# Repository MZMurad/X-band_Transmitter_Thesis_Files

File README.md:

# X-band_Transmitter_Thesis_Files
This is a repo for all the files used and mentioned in my thesis

The file structure:
    
- Hardware: Includes all KiCad schematics and PCBs, all are KiCad projects
- All GNU Radio flow graphs wthin the GNU labeled folder
- The python folder contains all python used for plotting and test automation for the HP5262A VNA and the HP8562A Spectrum Analyzer
- The data folder contains all data collected over the span of this thesis

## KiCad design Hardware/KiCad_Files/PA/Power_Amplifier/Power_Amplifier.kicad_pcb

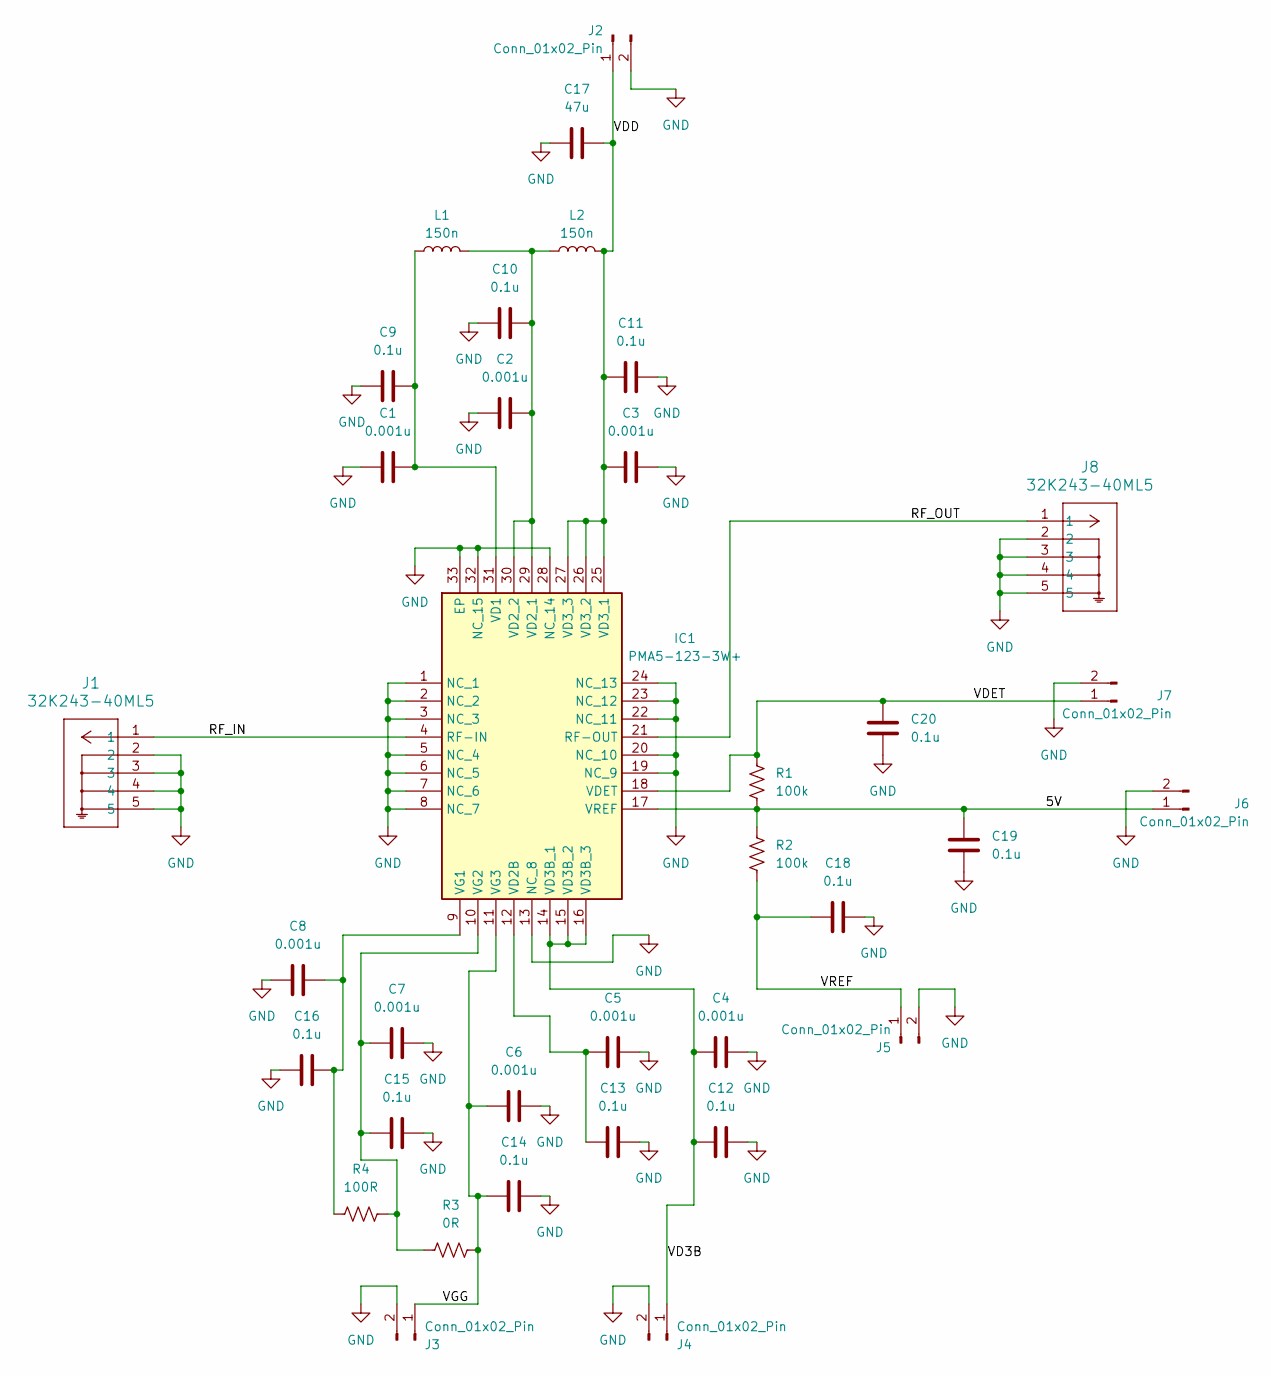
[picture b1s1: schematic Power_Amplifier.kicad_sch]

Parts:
C1, C2, C3, C4, C5, C6, C7, C8: 0.001u; C_0402_1005Metric_Pad0.74x0.62mm_HandSolder
C9, C10, C11, C12, C13, C14, C15, C16, C18, C19, C20: 0.1u; C_0402_1005Metric_Pad0.74x0.62mm_HandSolder
C17: 47u; C_1206_3216Metric
IC1: PMA5-123-3W+; QFN50P500X500X100-33N-D; Manufacturer_Part_Number PMA5-123-3W+
J1, J8: 32K243-40ML5; CONN_32K243-40ML5_RBG
J2, J3, J4, J5, J6, J7: Conn_01x02_Pin; PinHeader_1x02_P2.54mm_Vertical
L1, L2: 150n; L_0402_1005Metric_Pad0.77x0.64mm_HandSolder
R1, R2: 100k; R_0402_1005Metric_Pad0.72x0.64mm_HandSolder
R3: 0R; R_0402_1005Metric_Pad0.72x0.64mm_HandSolder
R4: 100R; R_0402_1005Metric_Pad0.72x0.64mm_HandSolder

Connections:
/5V: C19.1, IC1.17 (VREF), J6.1, R1.2, R2.1
/RF_IN: IC1.4 (RF-IN), J1.1
/RF_OUT: IC1.21 (RF-OUT), J8.1
/VD3B: C4.2, C12.2, IC1.14 (VD3B_1), IC1.15 (VD3B_2), IC1.16 (VD3B_3), J4.1
/VDD: C3.2, C11.1, C17.2, IC1.25 (VD3_1), IC1.26 (VD3_2), IC1.27 (VD3_3), J2.1, L2.2
/VDET: C20.1, IC1.18 (VDET), J7.1, R1.1
/VGG: C6.2, C14.2, IC1.11 (VG3), J3.1, R3.2
/VREF: C18.2, J5.1, R2.2
GND: C1.1, C2.1, C3.1, C4.1, C5.1, C6.1, C7.1, C8.1, C9.1, C10.1, C11.2, C12.1, C13.1, C14.1, C15.1, C16.1, C17.1, C18.1, C19.2, C20.2, IC1.1 (NC_1), IC1.2 (NC_2), IC1.3 (NC_3), IC1.5 (NC_4), IC1.6 (NC_5), IC1.7 (NC_6), IC1.8 (NC_7), IC1.13 (NC_8), IC1.19 (NC_9), IC1.20 (NC_10), IC1.22 (NC_11), IC1.23 (NC_12), IC1.24 (NC_13), IC1.28 (NC_14), IC1.32 (NC_15), IC1.33 (EP), J1.2, J1.3, J1.4, J1.5, J2.2, J3.2, J4.2, J5.2, J6.2, J7.2, J8.2, J8.3, J8.4, J8.5
unnamed: C1.2, C9.2, IC1.31 (VD1), L1.1
unnamed: C5.2, C13.2, IC1.12 (VD2B)
unnamed: C2.2, C10.2, IC1.29 (VD2_1), IC1.30 (VD2_2), L1.2, L2.1
unnamed: C8.2, C16.2, IC1.9 (VG1), R4.1
unnamed: C7.2, C15.2, IC1.10 (VG2), R3.1, R4.2

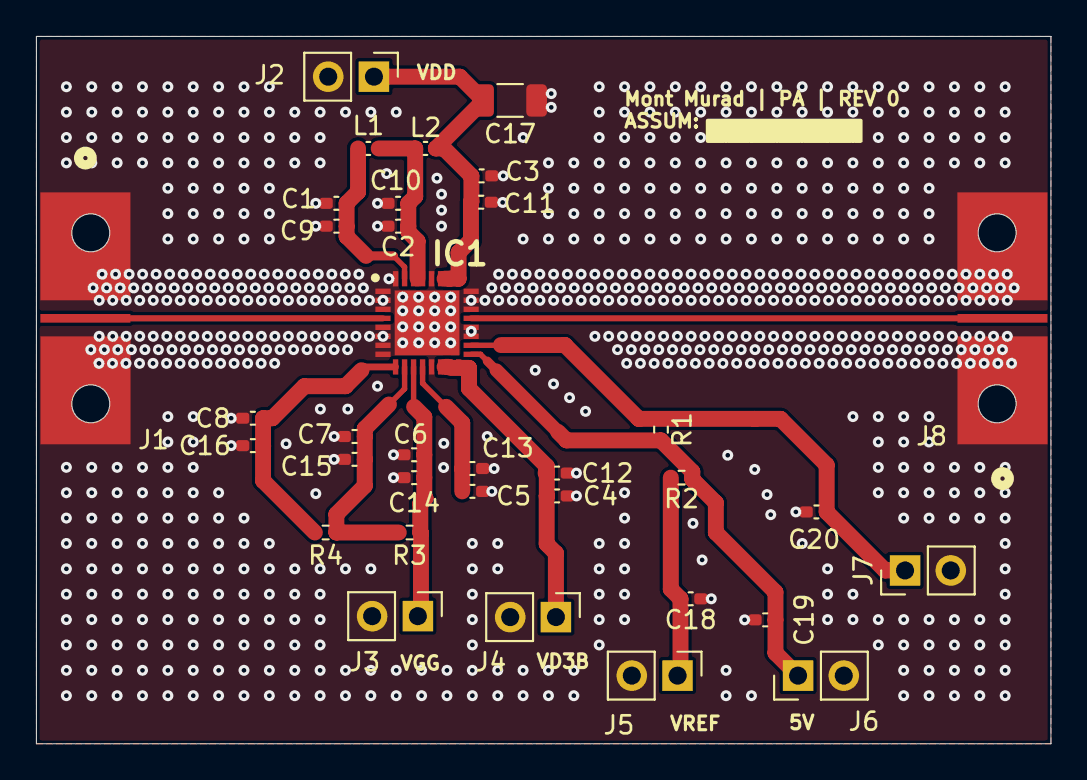
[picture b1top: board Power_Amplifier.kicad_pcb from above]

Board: 4 copper layers, 56.4 x 39.3 mm, 35 parts (0 on the bottom side), 14 nets.

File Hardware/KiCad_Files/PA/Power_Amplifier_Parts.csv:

"Reference","Value","Datasheet","Footprint","Qty","DNP"
"C1,C2,C3,C4,C5,C6,C7,C8","0.001u","~","Capacitor_SMD:C_0402_1005Metric_Pad0.74x0.62mm_HandSolder","8",""
"C9,C10,C11,C12,C13,C14,C15,C16,C18,C19,C20","0.1u","~","Capacitor_SMD:C_0402_1005Metric_Pad0.74x0.62mm_HandSolder","11",""
"C17","47u","~","Capacitor_SMD:C_1206_3216Metric","1",""
"IC1","PMA5-123-3W+","https://www.minicircuits.com/pdfs/PMA5-123-3W+.pdf","PMA5-123-3W+:QFN50P500X500X100-33N-D","1",""
"J1,J8","32K243-40ML5","32K243-40ML5","32K243-40ML5:CONN_32K243-40ML5_RBG","2",""
"J2,J3,J4,J5,J6,J7","Conn_01x02_Pin","~","Connector_PinHeader_2.54mm:PinHeader_1x02_P2.54mm_Vertical","6",""
"L1,L2","150n","~","Inductor_SMD:L_0402_1005Metric_Pad0.77x0.64mm_HandSolder","2",""
"R1,R2","100k","~","Resistor_SMD:R_0402_1005Metric_Pad0.72x0.64mm_HandSolder","2",""
"R3","0R","~","Resistor_SMD:R_0402_1005Metric_Pad0.72x0.64mm_HandSolder","1",""
"R4","100R","~","Resistor_SMD:R_0402_1005Metric_Pad0.72x0.64mm_HandSolder","1",""

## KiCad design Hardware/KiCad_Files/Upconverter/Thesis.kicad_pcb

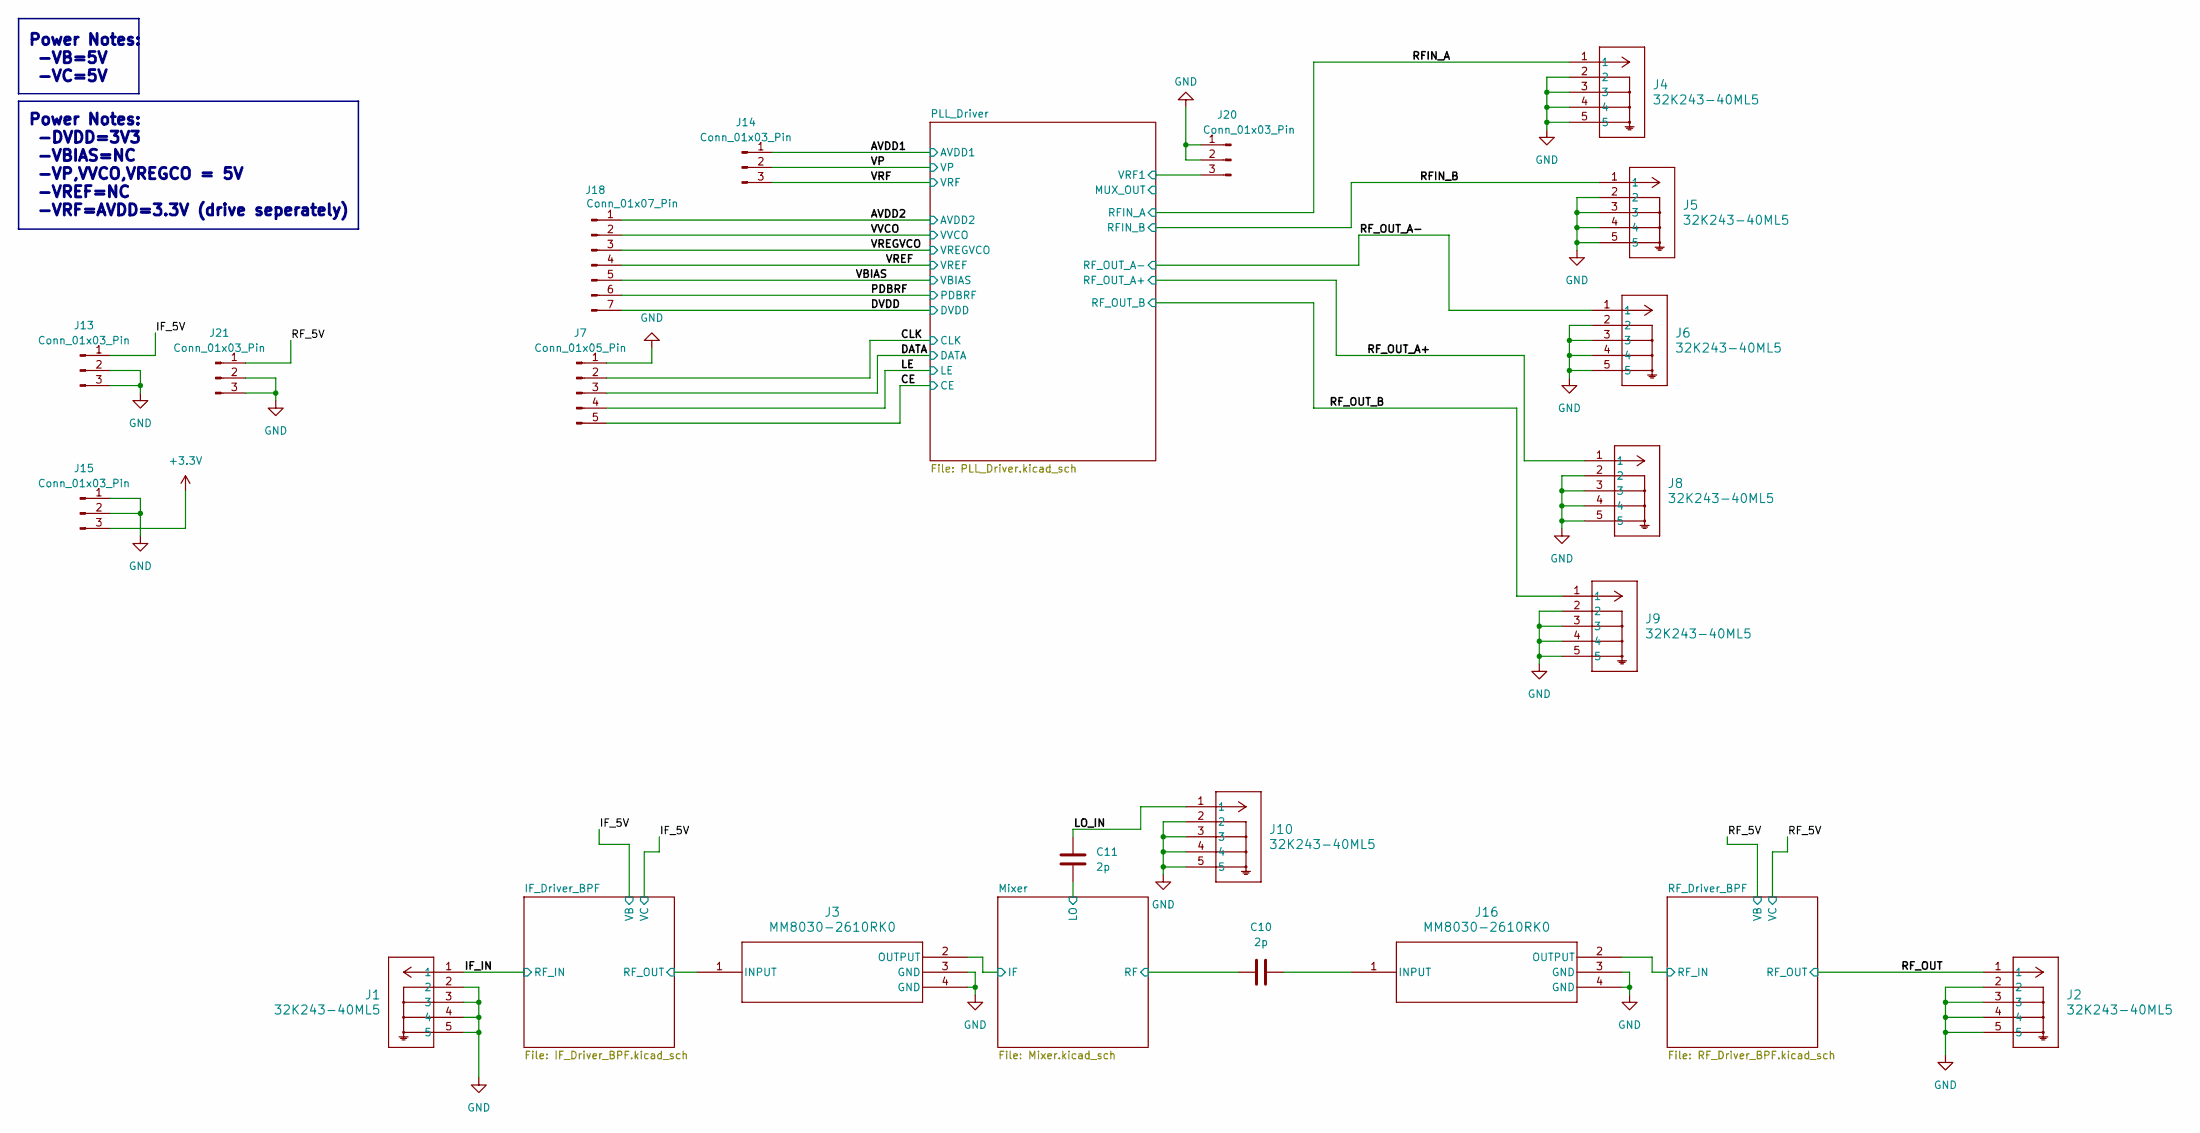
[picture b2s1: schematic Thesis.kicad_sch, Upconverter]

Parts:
C10, C11: 2p; C_0402_1005Metric_Pad0.74x0.62mm_HandSolder
J1, J2, J4, J5, J6, J8, J9, J10: 32K243-40ML5; CONN_32K243-40ML5_RBG
J3, J16: MM8030-2610RK0; MM8030-2610RK0_MUR
J7: Conn_01x05_Pin; PinHeader_1x05_P2.54mm_Vertical
J13, J14, J15, J20, J21: Conn_01x03_Pin; PinHeader_1x03_P2.54mm_Vertical
J18: Conn_01x07_Pin; PinHeader_1x07_P2.54mm_Vertical

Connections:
+3.3V: J15.3; also elsewhere on the board
/AVDD1: J14.1; also elsewhere on the board
/AVDD2: J18.1; also elsewhere on the board
/CE: J7.5; also elsewhere on the board
/CLK: J7.2; also elsewhere on the board
/DATA: J7.3; also elsewhere on the board
/DVDD: J18.7; also elsewhere on the board
/IF_5V: J13.1; also elsewhere on the board
/IF_Driver_BPF/RF_OUT: J3.1 (INPUT); also elsewhere on the board
/IF_IN: J1.1; also elsewhere on the board
/LE: J7.4; also elsewhere on the board
/LO_IN: C11.2, J10.1
/Mixer/IF: J3.2 (OUTPUT); also elsewhere on the board
/Mixer/LO: C11.1; also elsewhere on the board
/Mixer/RF: C10.1; also elsewhere on the board
/PDBRF: J18.6; also elsewhere on the board
/PLL_Driver/VRF1: J20.3; also elsewhere on the board
/RFIN_A: J4.1; also elsewhere on the board
/RFIN_B: J5.1; also elsewhere on the board
/RF_5V: J21.1; also elsewhere on the board
/RF_Driver_BPF/RF_IN: J16.2 (OUTPUT); also elsewhere on the board
/RF_OUT: J2.1; also elsewhere on the board
/RF_OUT_A+: J8.1; also elsewhere on the board
/RF_OUT_A-: J6.1; also elsewhere on the board
/RF_OUT_B: J9.1; also elsewhere on the board
/VBIAS: J18.5; also elsewhere on the board
/VP: J14.2; also elsewhere on the board
/VREF: J18.4; also elsewhere on the board
/VREGVCO: J18.3; also elsewhere on the board
/VRF: J14.3; also elsewhere on the board
/VVCO: J18.2; also elsewhere on the board
GND: J1.2, J1.3, J1.4, J1.5, J2.2, J2.3, J2.4, J2.5, J3.3 (GND), J3.4 (GND), J4.2, J4.3, J4.4, J4.5, J5.2, J5.3, J5.4, J5.5, J6.2, J6.3, J6.4, J6.5, J7.1, J8.2, J8.3, J8.4, J8.5, J9.2, J9.3, J9.4, J9.5, J10.2, J10.3, J10.4, J10.5, J13.2, J13.3, J15.1, J15.2, J16.3 (GND), J16.4 (GND), J20.1, J20.2, J21.2, J21.3; also elsewhere on the board
unnamed: C10.2, J16.1 (INPUT)

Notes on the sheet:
Power Notes: -DVDD=3V3 -VBIAS=NC -VP,VVCO,VREGCO = 5V -VREF=NC -VRF=AVDD=3.3V (drive seperately)
Power Notes: -VB=5V -VC=5V

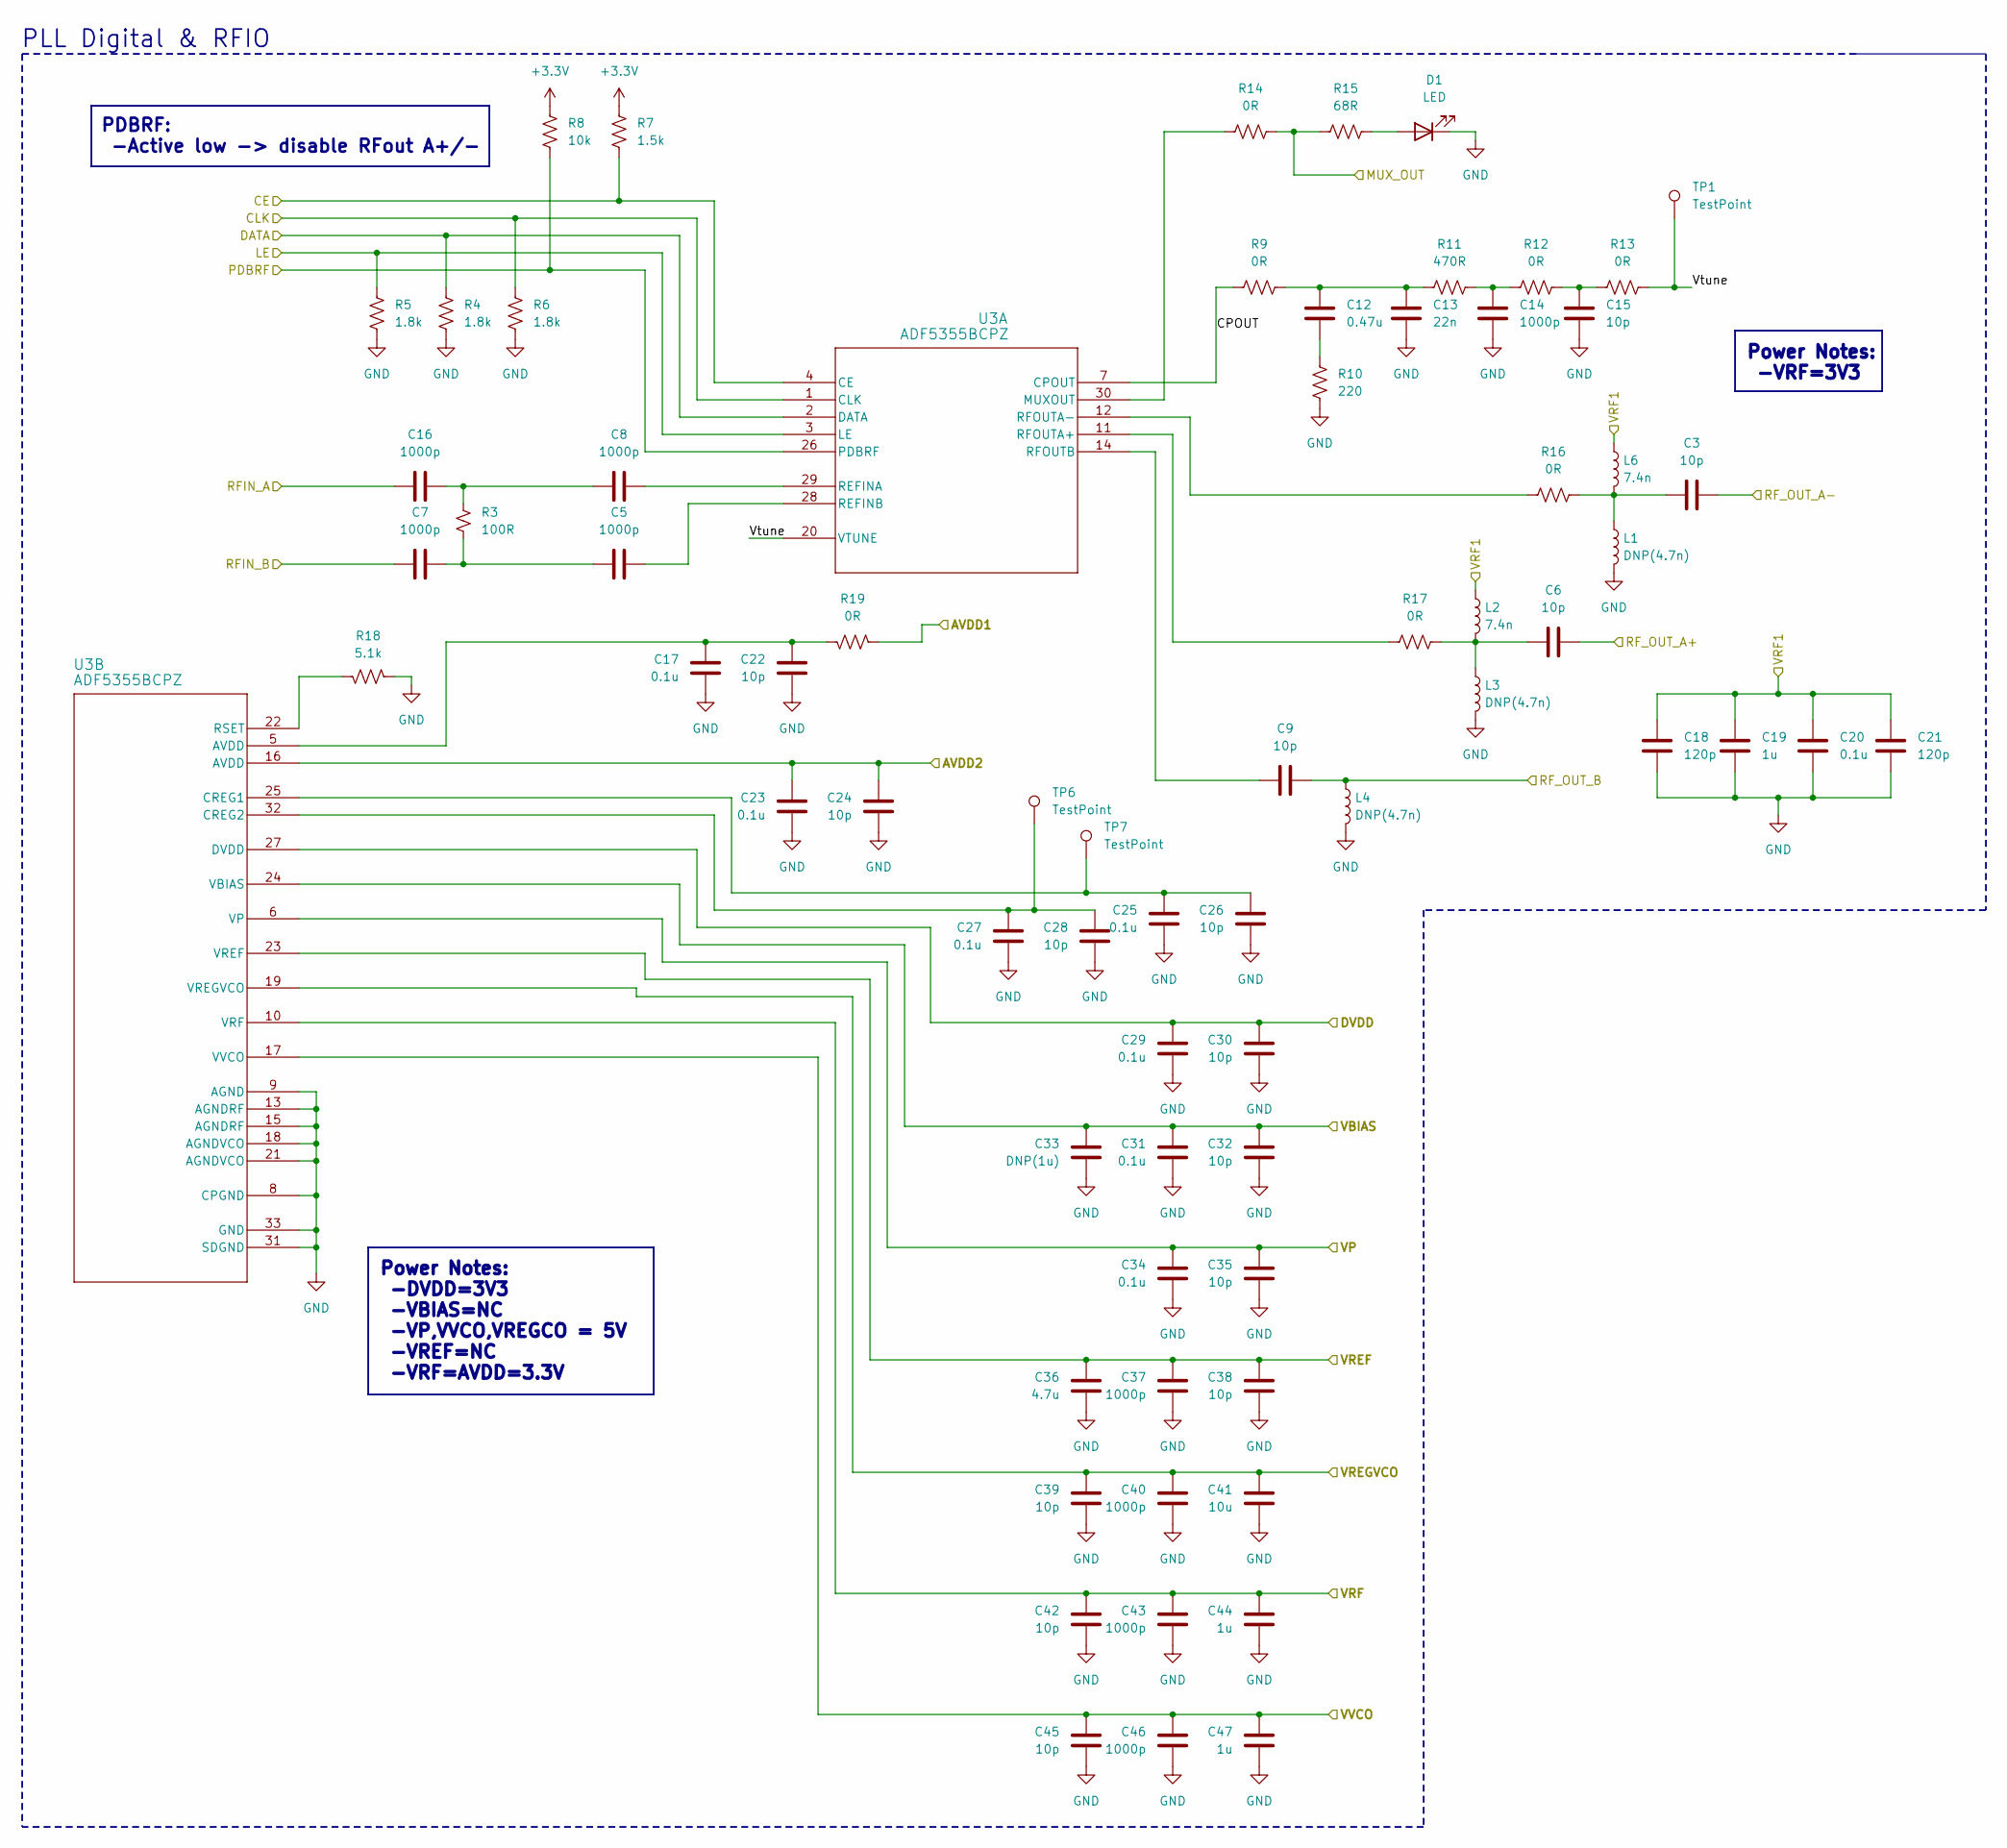
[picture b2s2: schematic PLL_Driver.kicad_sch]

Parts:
C3, C6, C9: 10p; C_0201_0603Metric_Pad0.64x0.40mm_HandSolder
C5, C7, C8, C16, C37, C40, C43, C46: 1000p; C_0402_1005Metric_Pad0.74x0.62mm_HandSolder
C12: 0.47u; C_0603_1608Metric_Pad1.08x0.95mm_HandSolder
C13: 22n; C_0603_1608Metric_Pad1.08x0.95mm_HandSolder
C14: 1000p; C_0603_1608Metric_Pad1.08x0.95mm_HandSolder
C15: 10p; C_0603_1608Metric_Pad1.08x0.95mm_HandSolder
C17, C23, C25, C27, C29, C31, C34: 0.1u; C_0402_1005Metric_Pad0.74x0.62mm_HandSolder
C18, C21: 120p; C_0603_1608Metric_Pad1.08x0.95mm_HandSolder
C19: 1u; C_0603_1608Metric_Pad1.08x0.95mm_HandSolder
C20: 0.1u; C_0603_1608Metric_Pad1.08x0.95mm_HandSolder
C22, C24, C26, C28, C30, C32, C35, C38, C39, C42, C45: 10p; C_0402_1005Metric_Pad0.74x0.62mm_HandSolder
C33: DNP(1u); C_0402_1005Metric_Pad0.74x0.62mm_HandSolder
C36: 4.7u; C_0402_1005Metric_Pad0.74x0.62mm_HandSolder
C41: 10u; C_0402_1005Metric_Pad0.74x0.62mm_HandSolder
C44, C47: 1u; C_0402_1005Metric_Pad0.74x0.62mm_HandSolder
D1: LED; LED_0603_1608Metric_Pad1.05x0.95mm_HandSolder
L1, L3, L4: DNP(4.7n); L_0201_0603Metric_Pad0.64x0.40mm_HandSolder
L2, L6: 7.4n; L_0201_0603Metric_Pad0.64x0.40mm_HandSolder
R3: 100R; R_0402_1005Metric_Pad0.72x0.64mm_HandSolder
R4, R5, R6: 1.8k; R_0603_1608Metric_Pad0.98x0.95mm_HandSolder
R7: 1.5k; R_0603_1608Metric_Pad0.98x0.95mm_HandSolder
R8: 10k; R_0603_1608Metric_Pad0.98x0.95mm_HandSolder
R9, R12, R13, R14, R19: 0R; R_0603_1608Metric_Pad0.98x0.95mm_HandSolder
R10: 220; R_0603_1608Metric_Pad0.98x0.95mm_HandSolder
R11: 470R; R_0603_1608Metric_Pad0.98x0.95mm_HandSolder
R15: 68R; R_0603_1608Metric_Pad0.98x0.95mm_HandSolder
R16, R17: 0R; R_0201_0603Metric_Pad0.64x0.40mm_HandSolder
R18: 5.1k; R_0603_1608Metric_Pad0.98x0.95mm_HandSolder
TP1: TestPoint; TestPoint_Pad_D1.5mm
TP6, TP7: TestPoint; TestPoint_Pad_D1.0mm
U3: ADF5355BCPZ; CP-32-12_ADI

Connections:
+3.3V: R7.1, R8.1; also elsewhere on the board
/AVDD1: R19.1; also elsewhere on the board
/AVDD2: C23.1, C24.1, U3.16 (AVDD); also elsewhere on the board
/CE: R7.2, U3.4 (CE); also elsewhere on the board
/CLK: R6.1, U3.1 (CLK); also elsewhere on the board
/DATA: R4.1, U3.2 (DATA); also elsewhere on the board
/DVDD: C29.1, C30.1, U3.27 (DVDD); also elsewhere on the board
/LE: R5.1, U3.3 (LE); also elsewhere on the board
/PDBRF: R8.2, U3.26 (PDBRF); also elsewhere on the board
/PLL_Driver/CPOUT: R9.1, U3.7 (CPOUT)
/PLL_Driver/MUX_OUT: R14.2, R15.1
/PLL_Driver/VRF1: C18.1, C19.1, C20.1, C21.1, L2.1, L6.1; also elsewhere on the board
/PLL_Driver/Vtune: R13.2, TP1.1, U3.20 (VTUNE)
/RFIN_A: C16.1; also elsewhere on the board
/RFIN_B: C7.1; also elsewhere on the board
/RF_OUT_A+: C6.2; also elsewhere on the board
/RF_OUT_A-: C3.2; also elsewhere on the board
/RF_OUT_B: C9.1, L4.1; also elsewhere on the board
/VBIAS: C31.1, C32.1, C33.1, U3.24 (VBIAS); also elsewhere on the board
/VP: C34.1, C35.1, U3.6 (VP); also elsewhere on the board
/VREF: C36.1, C37.1, C38.1, U3.23 (VREF); also elsewhere on the board
/VREGVCO: C39.1, C40.1, C41.1, U3.19 (VREGVCO); also elsewhere on the board
/VRF: C42.1, C43.1, C44.1, U3.10 (VRF); also elsewhere on the board
/VVCO: C45.1, C46.1, C47.1, U3.17 (VVCO); also elsewhere on the board
GND: C13.2, C14.2, C15.2, C17.2, C18.2, C19.2, C20.2, C21.2, C22.2, C23.2, C24.2, C25.2, C26.2, C27.2, C28.2, C29.2, C30.2, C31.2, C32.2, C33.2, C34.2, C35.2, C36.2, C37.2, C38.2, C39.2, C40.2, C41.2, C42.2, C43.2, C44.2, C45.2, C46.2, C47.2, D1.1 (K), L1.2, L3.2, L4.2, R4.2, R5.2, R6.2, R10.1, R18.1, U3.8 (CPGND), U3.9 (AGND), U3.13 (AGNDRF), U3.15 (AGNDRF), U3.18 (AGNDVCO), U3.21 (AGNDVCO), U3.31 (SDGND), U3.33 (GND); also elsewhere on the board
unnamed: C3.1, L1.1, L6.2, R16.2
unnamed: C5.1, C7.2, R3.2
unnamed: C6.1, L2.2, L3.1, R17.2
unnamed: C12.1, C13.1, R9.2, R11.1
unnamed: C12.2, R10.2
unnamed: C14.1, R11.2, R12.1
unnamed: C15.1, R12.2, R13.1
unnamed: C8.1, C16.2, R3.1
unnamed: C17.1, C22.1, R19.2, U3.5 (AVDD)
unnamed: D1.2 (A), R15.2
unnamed: R14.1, U3.30 (MUXOUT)
unnamed: C8.2, U3.29 (REFINA)
unnamed: C5.2, U3.28 (REFINB)
unnamed: R17.1, U3.11 (RFOUTA+)
unnamed: R16.1, U3.12 (RFOUTA-)
unnamed: C9.2, U3.14 (RFOUTB)
unnamed: C25.1, C26.1, TP7.1, U3.25 (CREG1)
unnamed: C27.1, C28.1, TP6.1, U3.32 (CREG2)
unnamed: R18.2, U3.22 (RSET)

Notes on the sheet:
PDBRF: -Active low -> disable RFout A+/-
Power Notes: -DVDD=3V3 -VBIAS=NC -VP,VVCO,VREGCO = 5V -VREF=NC -VRF=AVDD=3.3V
Power Notes: -VRF=3V3
PLL Digital & RFIO

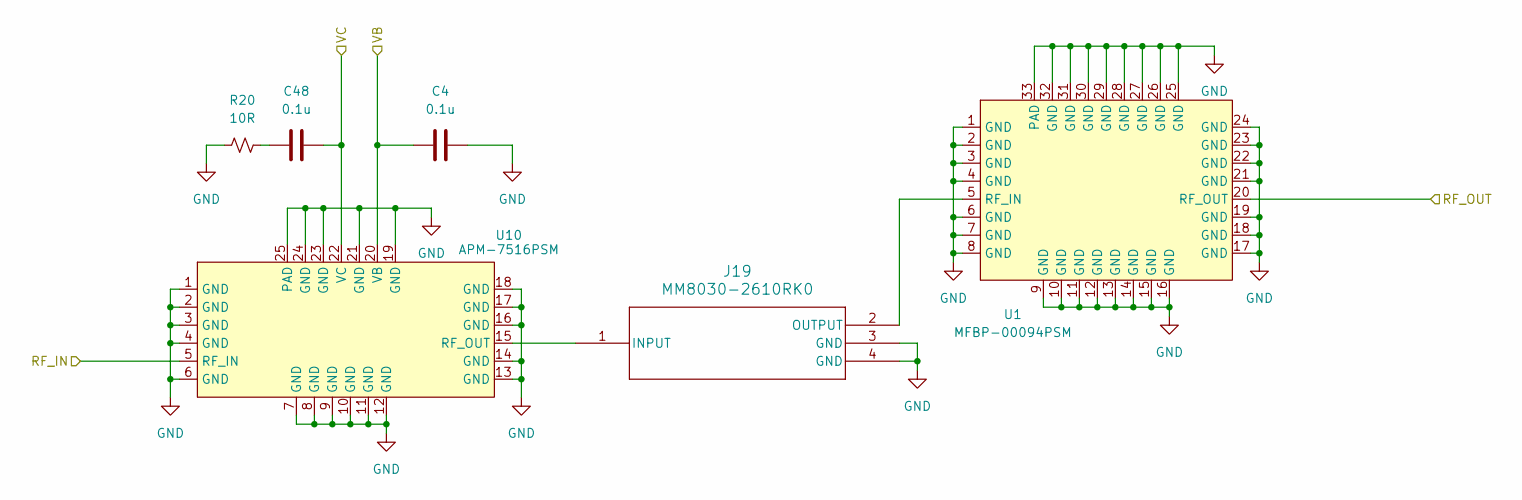
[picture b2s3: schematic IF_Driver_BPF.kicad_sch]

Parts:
C4, C48: 0.1u; C_0402_1005Metric_Pad0.74x0.62mm_HandSolder
J19: MM8030-2610RK0; MM8030-2610RK0_MUR
R20: 10R; R_0402_1005Metric_Pad0.72x0.64mm_HandSolder
U1: MFBP-00094PSM; QFN-32_EP_5x5_Pitch0.5mm
U10: APM-7516PSM; QFN-24_EP_4x4_Pitch0.5mm

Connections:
/IF_5V: C4.1, C48.2, U10.20 (VB), U10.22 (VC); also elsewhere on the board
/IF_Driver_BPF/RF_OUT: U1.20 (RF_OUT); also elsewhere on the board
/IF_IN: U10.5 (RF_IN); also elsewhere on the board
GND: C4.2, J19.3 (GND), J19.4 (GND), R20.1, U1.1 (GND), U1.2 (GND), U1.3 (GND), U1.4 (GND), U1.6 (GND), U1.7 (GND), U1.8 (GND), U1.9 (GND), U1.10 (GND), U1.11 (GND), U1.12 (GND), U1.13 (GND), U1.14 (GND), U1.15 (GND), U1.16 (GND), U1.17 (GND), U1.18 (GND), U1.19 (GND), U1.21 (GND), U1.22 (GND), U1.23 (GND), U1.24 (GND), U1.25 (GND), U1.26 (GND), U1.27 (GND), U1.28 (GND), U1.29 (GND), U1.30 (GND), U1.31 (GND), U1.32 (GND), U1.33 (PAD), U10.1 (GND), U10.2 (GND), U10.3 (GND), U10.4 (GND), U10.6 (GND), U10.7 (GND), U10.8 (GND), U10.9 (GND), U10.10 (GND), U10.11 (GND), U10.12 (GND), U10.13 (GND), U10.14 (GND), U10.16 (GND), U10.17 (GND), U10.18 (GND), U10.19 (GND), U10.21 (GND), U10.23 (GND), U10.24 (GND), U10.25 (PAD); also elsewhere on the board
unnamed: C48.1, R20.2
unnamed: J19.1 (INPUT), U10.15 (RF_OUT)
unnamed: J19.2 (OUTPUT), U1.5 (RF_IN)

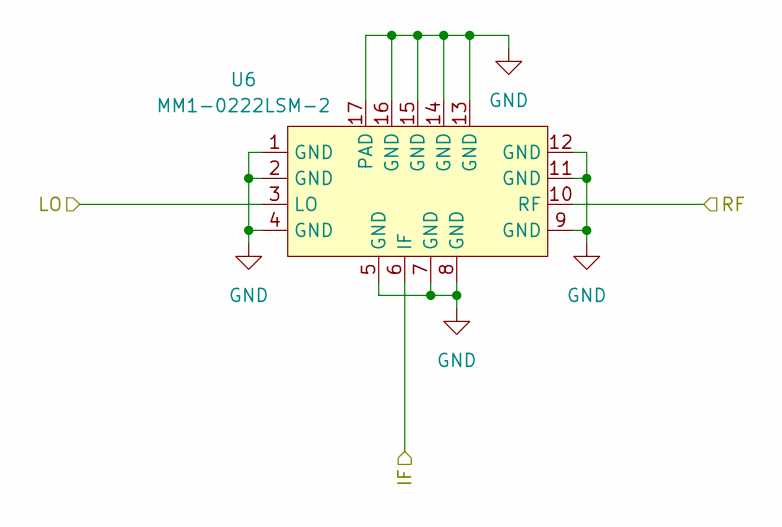
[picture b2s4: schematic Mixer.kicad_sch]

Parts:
U6: MM1-0222LSM-2; QFN-16_EP_3x3_Pitch0.5mm

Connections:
/Mixer/IF: U6.6 (IF); also elsewhere on the board
/Mixer/LO: U6.3 (LO); also elsewhere on the board
/Mixer/RF: U6.10 (RF); also elsewhere on the board
GND: U6.1 (GND), U6.2 (GND), U6.4 (GND), U6.5 (GND), U6.7 (GND), U6.8 (GND), U6.9 (GND), U6.11 (GND), U6.12 (GND), U6.13 (GND), U6.14 (GND), U6.15 (GND), U6.16 (GND), U6.17 (PAD); also elsewhere on the board

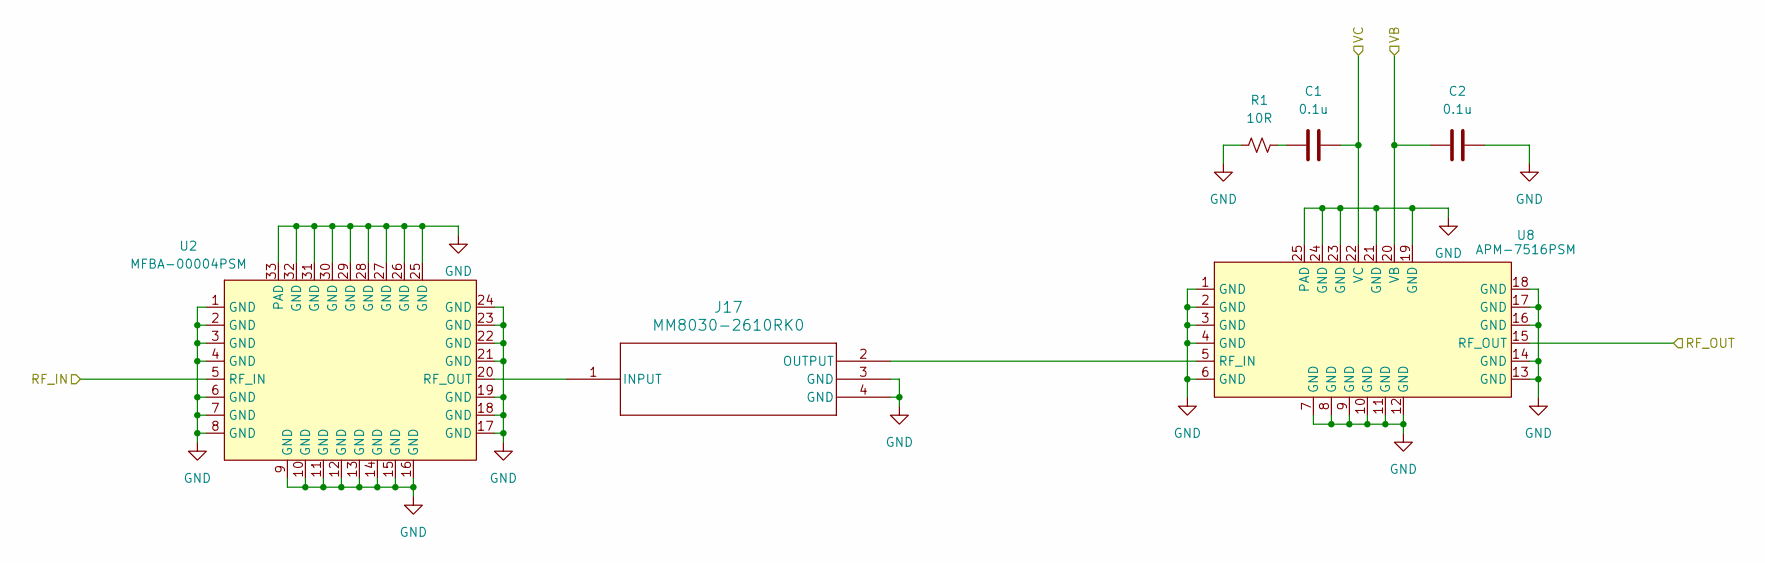
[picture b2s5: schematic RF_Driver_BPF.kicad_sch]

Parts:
C1, C2: 0.1u; C_0402_1005Metric_Pad0.74x0.62mm_HandSolder
J17: MM8030-2610RK0; MM8030-2610RK0_MUR
R1: 10R; R_0402_1005Metric_Pad0.72x0.64mm_HandSolder
U2: MFBA-00004PSM; QFN-32_EP_5x5_Pitch0.5mm
U8: APM-7516PSM; QFN-24_EP_4x4_Pitch0.5mm

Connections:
/RF_5V: C1.2, C2.1, U8.20 (VB), U8.22 (VC); also elsewhere on the board
/RF_Driver_BPF/RF_IN: U2.5 (RF_IN); also elsewhere on the board
/RF_OUT: U8.15 (RF_OUT); also elsewhere on the board
GND: C2.2, J17.3 (GND), J17.4 (GND), R1.1, U2.1 (GND), U2.2 (GND), U2.3 (GND), U2.4 (GND), U2.6 (GND), U2.7 (GND), U2.8 (GND), U2.9 (GND), U2.10 (GND), U2.11 (GND), U2.12 (GND), U2.13 (GND), U2.14 (GND), U2.15 (GND), U2.16 (GND), U2.17 (GND), U2.18 (GND), U2.19 (GND), U2.21 (GND), U2.22 (GND), U2.23 (GND), U2.24 (GND), U2.25 (GND), U2.26 (GND), U2.27 (GND), U2.28 (GND), U2.29 (GND), U2.30 (GND), U2.31 (GND), U2.32 (GND), U2.33 (PAD), U8.1 (GND), U8.2 (GND), U8.3 (GND), U8.4 (GND), U8.6 (GND), U8.7 (GND), U8.8 (GND), U8.9 (GND), U8.10 (GND), U8.11 (GND), U8.12 (GND), U8.13 (GND), U8.14 (GND), U8.16 (GND), U8.17 (GND), U8.18 (GND), U8.19 (GND), U8.21 (GND), U8.23 (GND), U8.24 (GND), U8.25 (PAD); also elsewhere on the board
unnamed: C1.1, R1.2
unnamed: J17.1 (INPUT), U2.20 (RF_OUT)
unnamed: J17.2 (OUTPUT), U8.5 (RF_IN)
